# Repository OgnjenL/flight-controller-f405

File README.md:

# STM32F405RGT6 Drone Flight Controller

## Custom-designed 4-layer Flight Controller

This project focuses on PCB design around the STM32F405 MCU. It features a 4-layer PCB with dedicated ground and power planes with an integrated IMU.

### Components and Specifications

* Microcontroller: STM32F405RGT6
* IMU: ICM-42670-P
* Power Management: 5V BUCK - LT8610, 3.3V LDO - LT1117-ADJ

The board is designed according to JLCPCB's manufacturing constraints, and the BOM is for LCSC parts.

1.  **Fabrication:** Upload the **V01.2_2.zip** file from the '/production' folder. Use a **4-layer** setting and a **1.6mm** board thickness.
2.  **Sourcing:** Use the provided **V01.2_2_bom.csv** file from the '/production' folder for automated part sourcing.
3.  **Assembly:** Reference the **V01.2_2_positions** file from the '/production' folder if using SMT assembly services, or use the silkscreen markings for manual soldering.
4.  **Datasheets:** STM32F405RGT6 - [stm32f405rg.pdf](https://github.com/user-attachments/files/26315604/stm32f405rg.pdf)
                    LT8610 - [LT8610 - datasheet.pdf](https://github.com/user-attachments/files/26315737/LT8610.-.datasheet.pdf)
                    LT1117 - [LT1117.PDF](https://github.com/user-attachments/files/26315667/LT1117.PDF)
                    ICM-42670-p - [ICM-42688-P.PDF](https://github.com/user-attachments/files/26315769/ICM-42688-P.PDF)

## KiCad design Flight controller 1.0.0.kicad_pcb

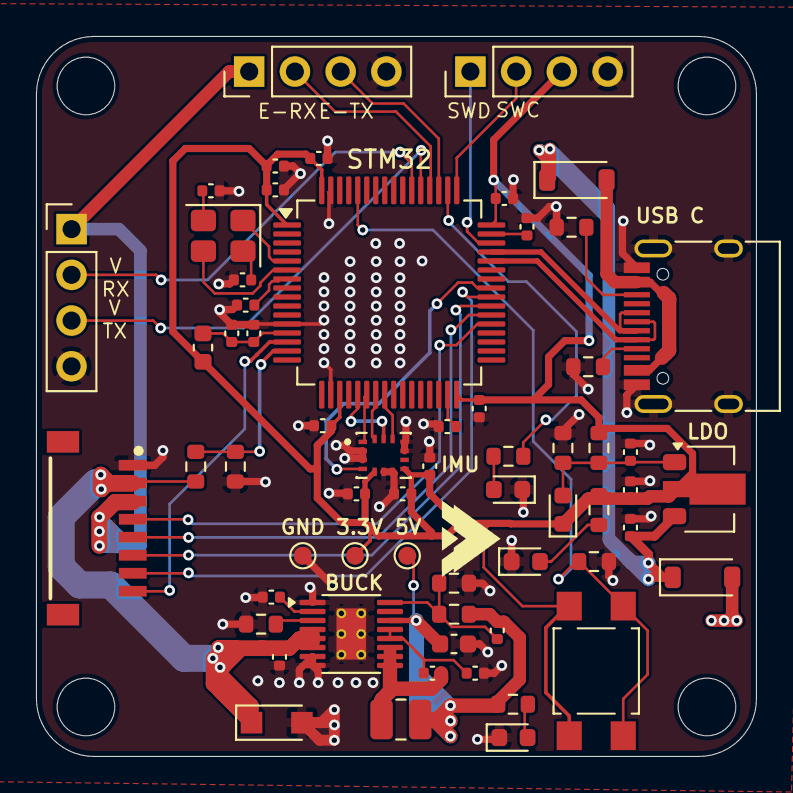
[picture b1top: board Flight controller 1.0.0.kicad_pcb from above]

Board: 4 copper layers, 40.0 x 40.0 mm, 61 parts (0 on the bottom side), 46 nets.

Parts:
3.3V: 3.3V; TestPoint_Pad_D1.0mm
5V: 5V; TestPoint_Pad_D1.0mm
BUCK: LT8610; MSOP-16-1EP_3x4.039mm_P0.5mm_EP1.651x2.845mm_ThermalVias
C1, C2, C3, C4, C5, C9, C12, C13, C17, C23, C24: 100n; C_0402_1005Metric
C6, C14, C15: 10u; C_0402_1005Metric
C7, C8, C11: 2.2u; C_0402_1005Metric
C10, C19, C22: 10n; C_0402_1005Metric
C16, C18, C25: 10p; C_0402_1005Metric
C21: 4.7u; C_0402_1005Metric
C26: 47u; C_0603_1608Metric
D1, D2: D_Schottky; D_SOD-123
D3, D4, D5: LED; LED_0603_1608Metric
D6: D_TVS; Nexperia_CFP3_SOD-123W
D8: D; D_0603_1608Metric
FB1: FerriteBead; L_0603_1608Metric
GND: GND; TestPoint_Pad_D1.0mm
J1: USB_C_Receptacle_USB2.0_14P; USB_C_Receptacle_HRO_TYPE-C-31-M-12
J2: Conn_01x08_Socket; JST_SM08B-SRSS-TB_LF__SN_
J3: Conn_01x04_Pin; PinHeader_1x04_P2.54mm_Vertical
J4, J5: Conn_01x04; PinHeader_1x04_P2.54mm_Vertical
L1: 10u; L_1008_2520Metric
LDO: LT1117-ADJ; SOT-89-3
MT1: ICM-42670-P; XDCR_ICM-42670-P
R1, R4: 10k; R_0603_1608Metric
R2, R3: 5.1k; R_0603_1608Metric
R5: 200; R_0603_1608Metric
R6: 121; R_0603_1608Metric
R7, R9, R13: 300; R_0603_1608Metric
R8: 1k; R_0603_1608Metric
R10: 110k; R_0603_1608Metric
R11: 243k; R_0603_1608Metric
R12: 1Meg; R_0603_1608Metric
STM32: STM32F405RGT6; LQFP-64_10x10mm_P0.5mm
SW1: SW_Push; SW_SPST_TL3305A
Y1: Crystal_GND24; Crystal_SMD_3225-4Pin_3.2x2.5mm

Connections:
+3.3V: 3.3V.1, C1.1, C2.1, C3.1, C4.1, C5.1, C6.1, C10.2, C11.2, C12.2, C15.1, D8.1 (K), FB1.1, J3.3, LDO.2 (VO), MT1.5 (VDDIO), MT1.8 (VDD), R6.1, R7.1, STM32.1 (VBAT), STM32.19 (VDD), STM32.32 (VDD), STM32.48 (VDD), STM32.64 (VDD), SW1.1
+5V: C13.1, D1.1 (K), D2.1 (K), LDO.3 (VI)
+5V_BUCK: 5V.1, BUCK.14 (BIAS), C25.2, C26.2, D2.2 (A), J2.3, J4.1, J5.1, L1.2, R12.2, R13.1
+5V_USB: D1.2 (A), J1.A4 (VBUS), J1.A9 (VBUS), J1.B4 (VBUS), J1.B9 (VBUS)
/+5V_BUCK_1: BUCK.9 (SW), BUCK.10 (SW), BUCK.11 (SW), C24.1, L1.1
/BOOT0: R1.2, STM32.60 (BOOT0), SW1.2
/CC1: J1.A5 (CC1), R3.1
/CC2: J1.B5 (CC2), R2.1
/LED_STM32: R9.1, STM32.50 (PA15)
/NRST: C9.1, STM32.7 (NRST)
/RCC_OSC_IN: STM32.5 (PH0), Y1.1
/RCC_OSC_OUT: STM32.6 (PH1), Y1.3
/TR/SS: BUCK.2 (TR/SS), C22.2
/VCAP1: C7.2, STM32.31 (VCAP_1)
/VCAP2: C8.2, STM32.47 (VCAP_2)
/VDDA: C17.1, C19.1, FB1.2, STM32.13 (VDDA)
Batt_control: R4.2, R8.1, STM32.15 (PA1)
Curr_sensor: J2.8, STM32.14 (PA0)
D+: J1.A6 (D+), J1.B6 (D+), STM32.45 (PA12)
D-: J1.A7 (D-), J1.B7 (D-), STM32.44 (PA11)
ELRS_RX: J5.2, STM32.52 (PC11)
ELRS_TX: J5.3, STM32.51 (PC10)
GND: BUCK.1 (SYNC), BUCK.7 (GND), BUCK.8 (GND), BUCK.17 (GND), C1.2, C2.2, C3.2, C4.2, C5.2, C6.2, C7.1, C8.1, C9.2, C10.1, C11.1, C12.1, C13.2, C14.2, C15.2, C16.1, C17.2, C18.1, C19.2, C21.2, C22.1, C23.2, C26.1, D3.1 (K), D4.1 (K), D5.1 (K), D6.2 (A2), GND.1, J1.A1 (GND), J1.A12 (GND), J1.B1 (GND), J1.B12 (GND), J1.S1 (SHIELD), J2.1, J3.4, J4.4, J5.4, MT1.2 (RESV), MT1.3 (RESV), MT1.6 (GND), MT1.7 (FSYNC), MT1.10 (RESV), MT1.11 (RESV), R1.1, R2.2, R3.2, R5.2, R8.2, R10.2, R11.2, STM32.12 (VSSA), STM32.18 (VSS), STM32.63 (VSS)
Interrupt: MT1.4 (INT1/INT), STM32.41 (PA8)
M1: J2.4, STM32.37 (PC6)
M2: J2.5, STM32.38 (PC7)
M3: J2.6, STM32.39 (PC8)
M4: J2.7, STM32.40 (PC9)
unnamed: C16.2, Y1.4
unnamed: C18.2, Y1.2
unnamed: D3.2 (A), R7.2
unnamed: D4.2 (A), R9.2
unnamed: D5.2 (A), R13.2
unnamed: C14.1, D8.2 (A), LDO.1 (ADJ), R5.1, R6.2
unnamed: BUCK.12 (BST), BUCK.13 (INTVcc), C23.1, C24.2
unnamed: BUCK.16 (FB), C25.1, R11.1, R12.1
unnamed: BUCK.3 (RT), R10.1
SPI1_CS: MT1.12 (AP_CS), STM32.24 (PC4)
SPI1_MISO: MT1.1 (AP_SDO/AP_AD0), STM32.22 (PA6)
SPI1_MOSI: MT1.14 (AP_SDA/AP_SDIO/AP_SDI), STM32.23 (PA7)
SPI1_SCK: MT1.13 (AP_SCL/AP_SCLK), STM32.21 (PA5)
SWCLK: J3.2, STM32.49 (PA14)
SWDIO: J3.1, STM32.46 (PA13)
VBat: BUCK.4 (EN/UV), BUCK.5 (VIN), BUCK.6 (VIN), C21.1, D6.1 (A1), J2.2, R4.1
VTX_RX: J4.2, STM32.54 (PD2)
VTX_TX: J4.3, STM32.53 (PC12)

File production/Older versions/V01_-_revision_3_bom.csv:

Designator,Quantity,Value,LCSC Part #
BUCK,1,LT8610,C462619
"C1, C12, C13, C17, C2, C23, C24, C3, C4, C5, C9",11,100n,C49062
"C10, C19, C22",3,10n,C76941
"C11, C7, C8",3,2.2u,C318539
"C14, C15, C6",3,10u,C315248
"C16, C18, C25",3,10p,C43535
C21,1,4.7u,C6119795
C26,1,47u,C178330
"D1, D2",2,D_Schottky,C5345968
"D3, D4, D5",3,LED,C19273151
D6,1,D_TVS,C49207092
D8,1,D,C30584800
FB1,1,FerriteBead,C107335
J1,1,USB_C_Receptacle_USB2.0_14P,C165948
J2,1,Conn_01x08_Socket,C265120
L1,1,10u,C53436344
LDO,1,LT1117-ADJ,C3014296
MT1,1,ICM-42670-P,C3288646
"R1, R4",2,10k,C98220
R10,1,110k,C2906984
R11,1,243k,C137764
R12,1,1Meg,C2907115
"R13, R7, R9",3,300,C2907148
"R2, R3",2,5.1k,C2907044
R5,1,200,C25804
R6,1,121,C2933134
R8,1,1k,C2907113
STM32,1,STM32F405RGT6,C15742
SW1,1,SW_Push,C2886902
Y1,1,Crystal_GND24,C2916927

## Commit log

2026-03-11 Initial commit: Konacna verzija
2026-03-17 Povecane komponente
2026-03-17 Kondenzatori-povecani
2026-03-18 ispocetka
2026-03-25 saving before reorganizing
2026-03-25 Update .gitignore and removing unwanted files
2026-03-25 Updating folder
2026-03-27 Update README with project details and specifications
    Added detailed project description, components, and specifications for the STM32F405RGT6 Drone Flight Controller.
2026-03-27 Added images
2026-03-27 Update images in README with local references
    Replaced old image links with local image references for front and back views.
2026-03-27 Fix image paths for front and back views
    Corrected image path casing in README.md
